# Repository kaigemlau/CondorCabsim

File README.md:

# Condor Cab Sim with Power Supply

Build with 15V symmetric power supply and active DI output (e.g. XLR)

Schematic and Layout created with KiCad 5

Original Design by Runoffgrove:
http://www.runoffgroove.com/condor.html

Works very well as an addon to the Anvil Preamp:
https://andyszeugs.wordpress.com/preamp-the-anvil/

## License: CC BY-NC-SA 3.0
Ref. original Condor Cab-Sim License:
https://creativecommons.org/licenses/by-nc-sa/3.0/

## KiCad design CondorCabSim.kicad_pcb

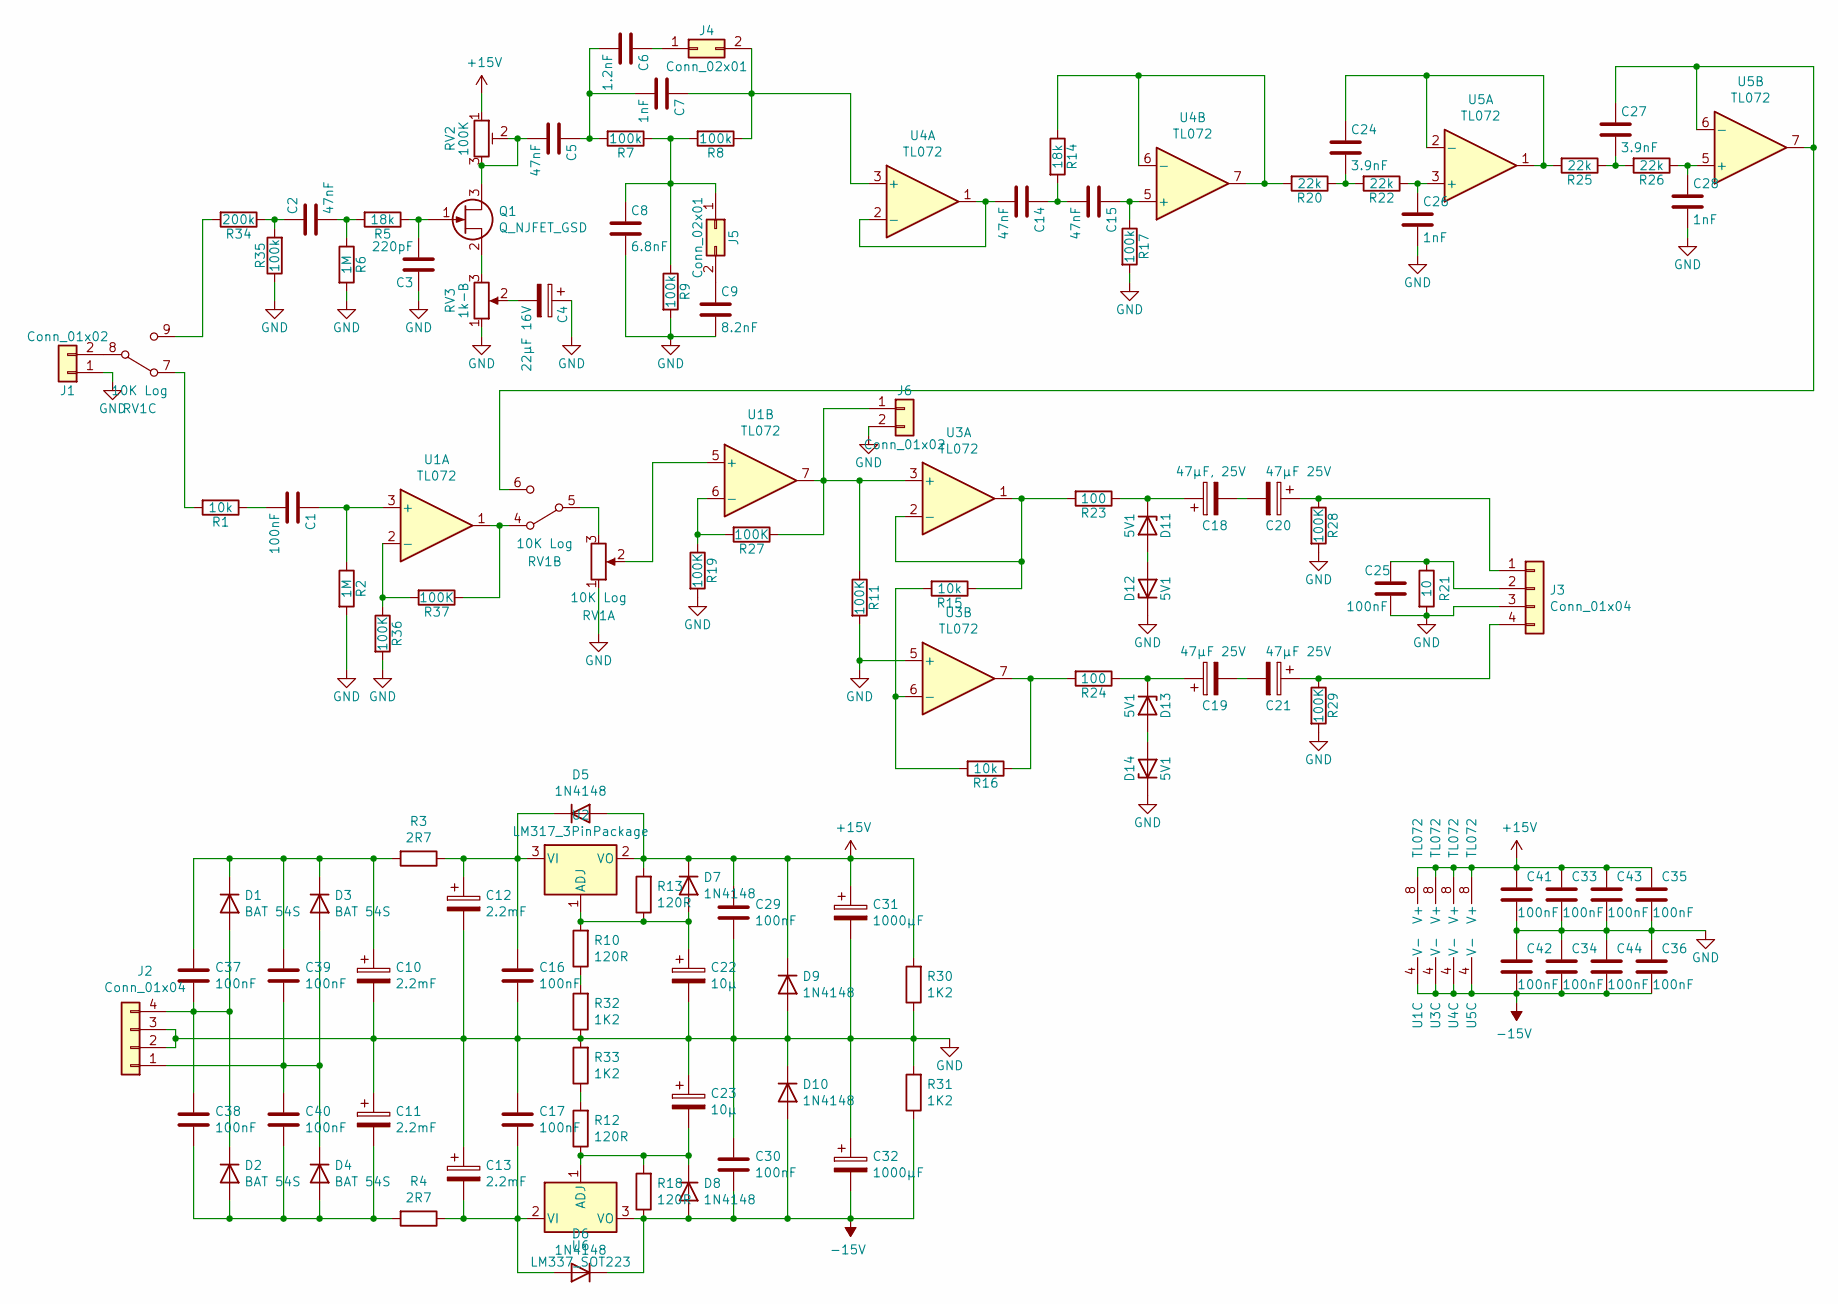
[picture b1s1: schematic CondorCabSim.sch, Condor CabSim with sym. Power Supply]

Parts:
C1: 100nF; C_Rect_L7.2mm_W2.5mm_P5.00mm_FKS2_FKP2_MKS2_MKP2
C2, C5, C14, C15: 47nF; C_Rect_L4.6mm_W3.0mm_P2.50mm_MKS02_FKP02
C3: 220pF; C_Rect_L4.6mm_W2.0mm_P2.50mm_MKS02_FKP02
C4: 22µF 16V; CP_Elec_4x5.8
C6: 1.2nF; C_Disc_D5.1mm_W3.2mm_P5.00mm
C7, C26, C28: 1nF; C_Rect_L4.6mm_W3.0mm_P2.50mm_MKS02_FKP02
C8: 6.8nF; C_Rect_L4.6mm_W3.0mm_P2.50mm_MKS02_FKP02
C9: 8.2nF; C_Disc_D5.1mm_W3.2mm_P5.00mm
C10, C11, C12, C13: 2.2mF; CP_Radial_D16.0mm_P7.50mm
C16, C17, C25, C29, C30, C33, C34, C35, C36, C37, C38, C39, C40, C41, C42, C43, C44: 100nF; C_0603_1608Metric
C18: 47µF, 25V; CP_Elec_6.3x5.8
C19, C20, C21: 47µF 25V; CP_Elec_6.3x5.8
C22, C23: 10µ; CP_Elec_5x5.9
C24, C27: 3.9nF; C_Disc_D5.1mm_W3.2mm_P5.00mm
C31, C32: 1000µF; CP_Radial_D10.0mm_P3.50mm
D1, D2, D3, D4: BAT 54S; D_DO-41_SOD81_P7.62mm_Horizontal
D5, D6, D7, D8, D9, D10: 1N4148; D_SOD-323F
D11, D12, D13, D14: 5V1; D_SOT-23_ANK
J1, J6: Conn_01x02; Molex_KK-254_AE-6410-02A_1x02_P2.54mm_Vertical
J2, J3: Conn_01x04; Molex_KK-254_AE-6410-04A_1x04_P2.54mm_Vertical
J4, J5: Conn_02x01; PinHeader_2x01_P2.54mm_Vertical
Q1: Q_NJFET_GSD; TO-92
R1, R15, R16: 10k; R_0603_1608Metric
R2, R6: 1M; R_0603_1608Metric
R3, R4: 2R7; R_1206_3216Metric
R5, R14: 18k; R_0603_1608Metric
R7, R8, R9, R17, R35: 100k; R_0603_1608Metric
R10, R12, R13, R18: 120R; R_0805_2012Metric
R11, R19, R27, R28, R29, R36, R37: 100K; R_0603_1608Metric
R20, R22, R25, R26: 22k; R_0603_1608Metric
R21: 10; R_0603_1608Metric
R23, R24: 100; R_0603_1608Metric
R30, R31: 1K2; R_1206_3216Metric
R32, R33: 1K2; R_0805_2012Metric
R34: 200k; R_0603_1608Metric
RV1: 10K Log; Potentiometer_Alpha_RV16BF-20_Single_Horizontal_DPDT
RV2: 100K; Potentiometer_Piher_PT-6-V_Vertical
RV3: 1k-B; Potentiometer_Alps_RK163_Single_Horizontal
U1, U3, U4, U5: TL072; SOIC-8_3.9x4.9mm_P1.27mm
U2: LM317_3PinPackage; SOT-223-3_TabPin2
U6: LM337_SOT223; SOT-223-3_TabPin2

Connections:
+15V: C29.1, C31.1, C33.1, C35.1, C41.1, C43.1, D5.2 (A), D7.1 (K), D9.1 (K), R13.2, R30.2, RV2.1, U1.8 (V+), U2.2 (VO), U3.8 (V+), U4.8 (V+), U5.8 (V+)
-15V: C30.2, C32.2, C34.2, C36.2, C42.2, C44.2, D6.1 (K), D8.2 (A), D10.2 (A), R18.1, R31.1, U1.4 (V-), U3.4 (V-), U4.4 (V-), U5.4 (V-), U6.3 (VO)
GND: C3.1, C4.1, C8.2, C9.2, C10.2, C11.1, C12.2, C13.1, C16.2, C17.1, C22.2, C23.1, C25.2, C26.2, C28.2, C29.2, C30.1, C31.2, C32.1, C33.2, C34.1, C35.2, C36.1, C41.2, C42.1, C43.2, C44.1, D9.2 (A), D10.1 (K), D12.1 (K), D14.1 (K), J1.1, J2.2, J2.3, J3.3, J6.2, R2.2, R6.2, R9.2, R11.2, R17.2, R19.2, R21.2, R28.2, R29.2, R30.1, R31.2, R32.1, R33.2, R35.1, R36.2, RV1.1, RV3.1, U3.5 (+)
unnamed: C1.1, R2.1, U1.3 (+)
unnamed: C1.2, R1.1
unnamed: C2.1, R34.1, R35.2
unnamed: C2.2, R5.2, R6.1
unnamed: C3.2, Q1.1 (G), R5.1
unnamed: C4.2, RV3.2
unnamed: C5.1, C6.2, C7.2, R7.2
unnamed: C5.2, Q1.3 (D), RV2.2, RV2.3
unnamed: C6.1, J4.1
unnamed: C7.1, J4.2, R8.1, U4.3 (+)
unnamed: C8.1, J5.1, R7.1, R8.2, R9.1
unnamed: C9.1, J5.2
unnamed: C10.1, C37.1, C39.1, D1.1 (K), D3.1 (K), R3.2
unnamed: C11.2, C38.2, C40.2, D2.2 (A), D4.2 (A), R4.2
unnamed: C12.1, C16.1, D5.1 (K), R3.1, U2.3 (VI)
unnamed: C13.2, C17.2, D6.2 (A), R4.1, U6.2 (VI)
unnamed: C14.1, C15.2, R14.2
unnamed: C14.2, U4.1, U4.2 (-)
unnamed: C15.1, R17.1, U4.5 (+)
unnamed: C18.1, D11.1 (K), R23.1
unnamed: C18.2, C20.2
unnamed: C19.1, D13.1 (K), R24.1
unnamed: C19.2, C21.2
unnamed: C20.1, J3.1, R28.1
unnamed: C21.1, J3.4, R29.1
unnamed: C22.1, D7.2 (A), R10.2, R13.1, U2.1 (ADJ)
unnamed: C23.2, D8.1 (K), R12.1, R18.2, U6.1 (ADJ)
unnamed: C24.1, R25.2, U5.1, U5.2 (-)
unnamed: C24.2, R20.1, R22.2
unnamed: C25.1, J3.2, R21.1
unnamed: C26.1, R22.1, U5.3 (+)
unnamed: C27.1, RV1.6, U5.6 (-), U5.7
unnamed: C27.2, R25.1, R26.2
unnamed: C28.1, R26.1, U5.5 (+)
unnamed: C37.2, C38.1, D1.2 (A), D2.1 (K), J2.4
unnamed: C39.2, C40.1, D3.2 (A), D4.1 (K), J2.1
unnamed: D11.2 (A), D12.2 (A)
unnamed: D13.2 (A), D14.2 (A)
unnamed: J1.2, RV1.8
unnamed: J6.1, R11.1, R27.1, U1.7, U3.3 (+)
unnamed: Q1.2 (S), RV3.3
unnamed: R1.2, RV1.7
unnamed: R10.1, R32.2
unnamed: R12.2, R33.1
unnamed: R14.1, R20.2, U4.6 (-), U4.7
unnamed: R15.1, R23.2, U3.1, U3.2 (-)
unnamed: R15.2, R16.2, U3.6 (-)
unnamed: R16.1, R24.2, U3.7
unnamed: R19.1, R27.2, U1.6 (-)
unnamed: R34.2, RV1.9
unnamed: R36.1, R37.2, U1.2 (-)
unnamed: R37.1, RV1.4, U1.1
unnamed: RV1.2, U1.5 (+)
unnamed: RV1.3, RV1.5

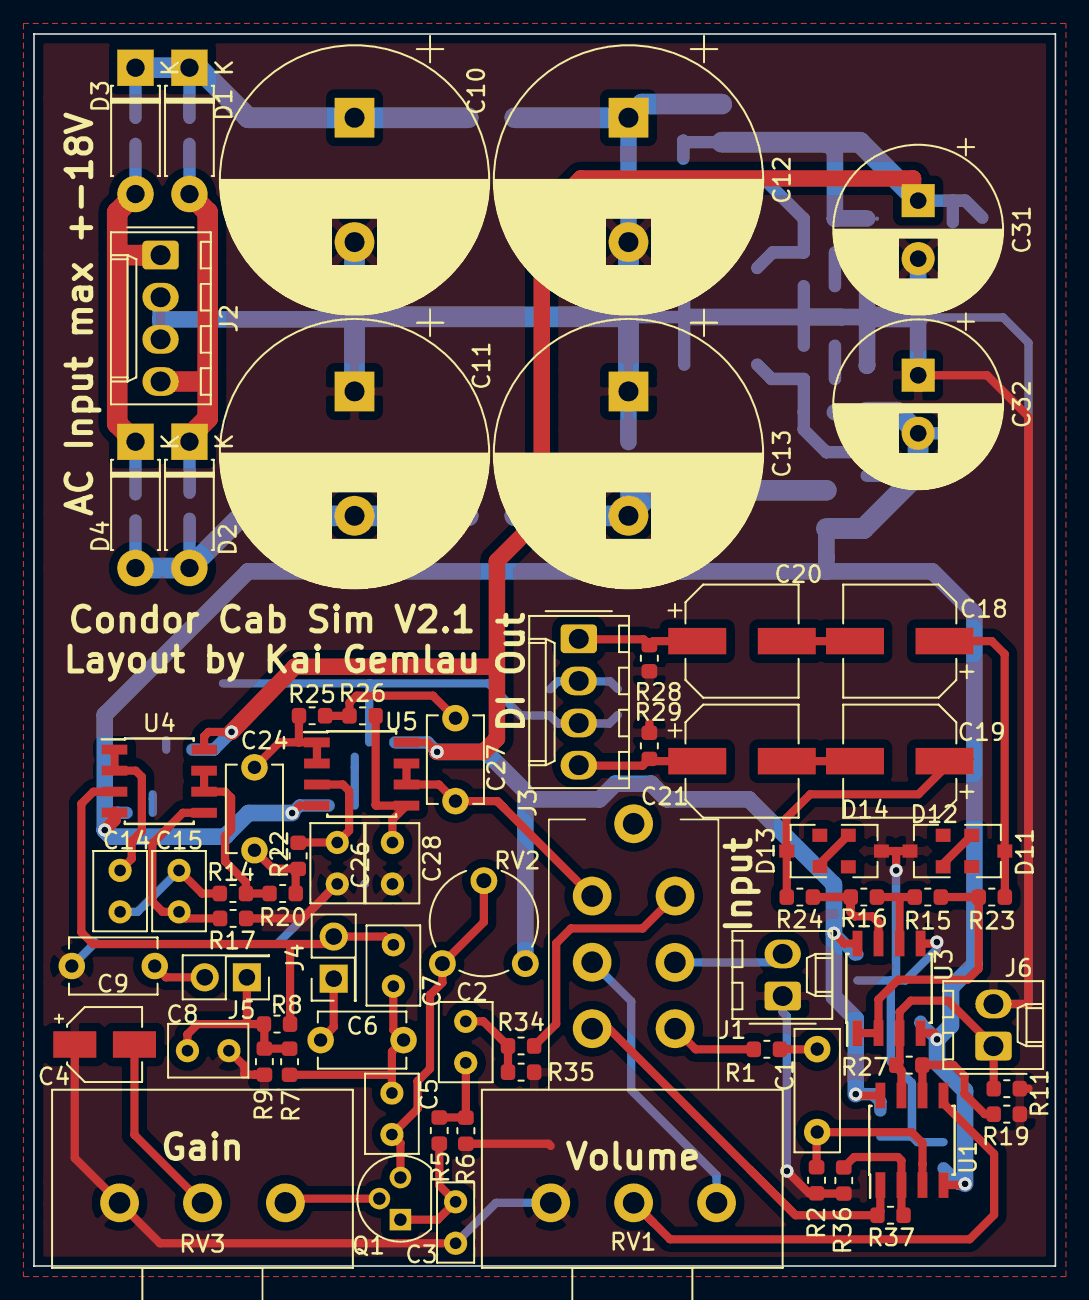
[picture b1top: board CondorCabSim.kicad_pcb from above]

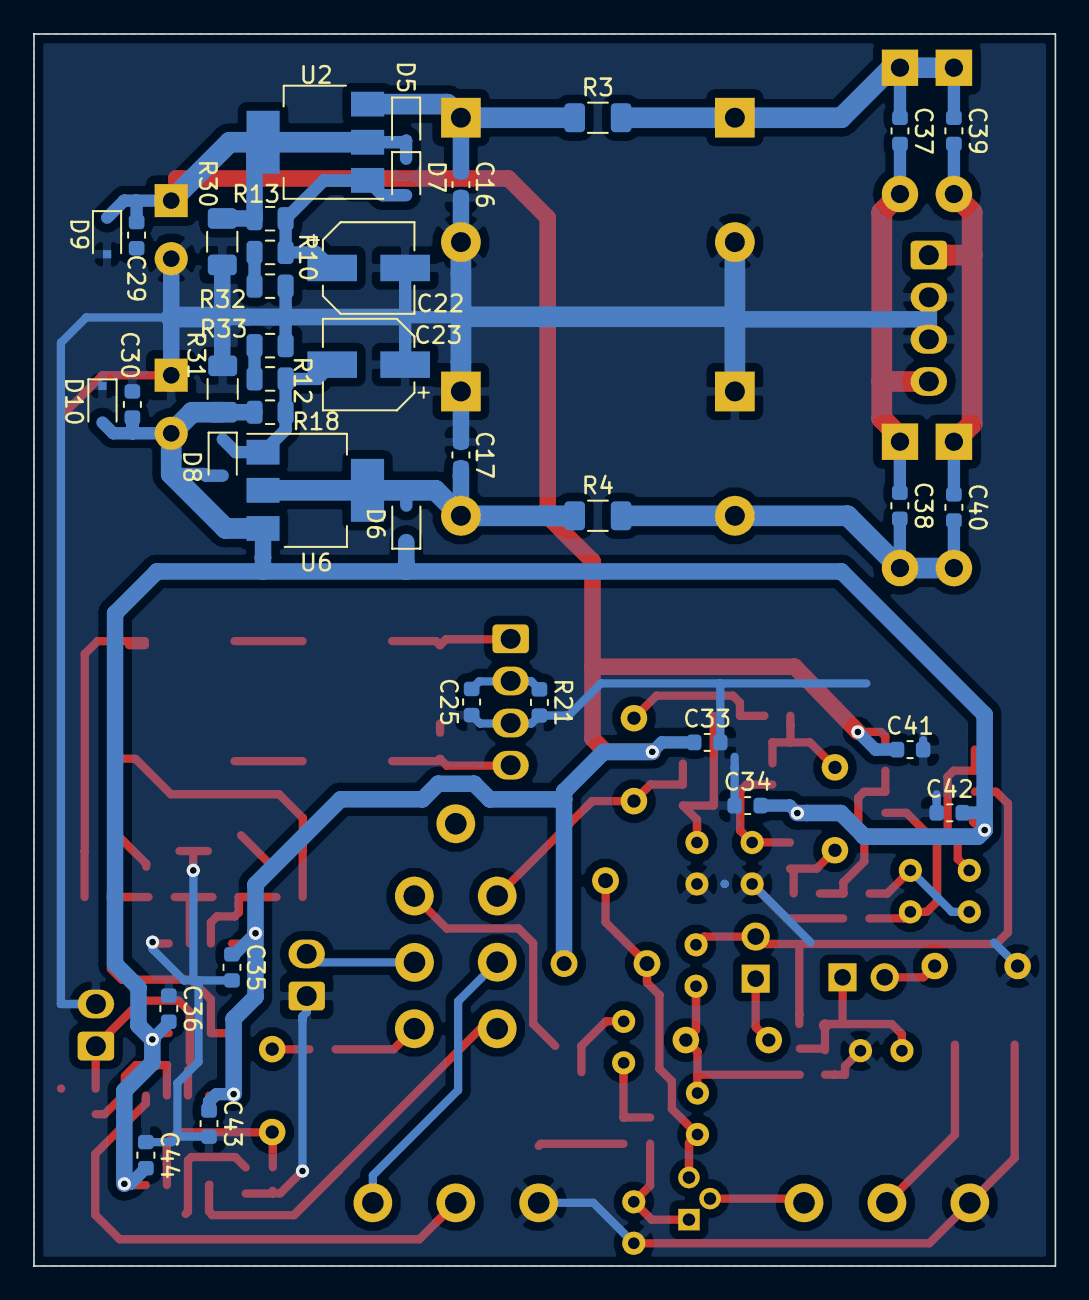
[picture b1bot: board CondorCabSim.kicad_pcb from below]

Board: 2 copper layers, 61.6 x 74.3 mm, 111 parts (38 on the bottom side), 57 nets.

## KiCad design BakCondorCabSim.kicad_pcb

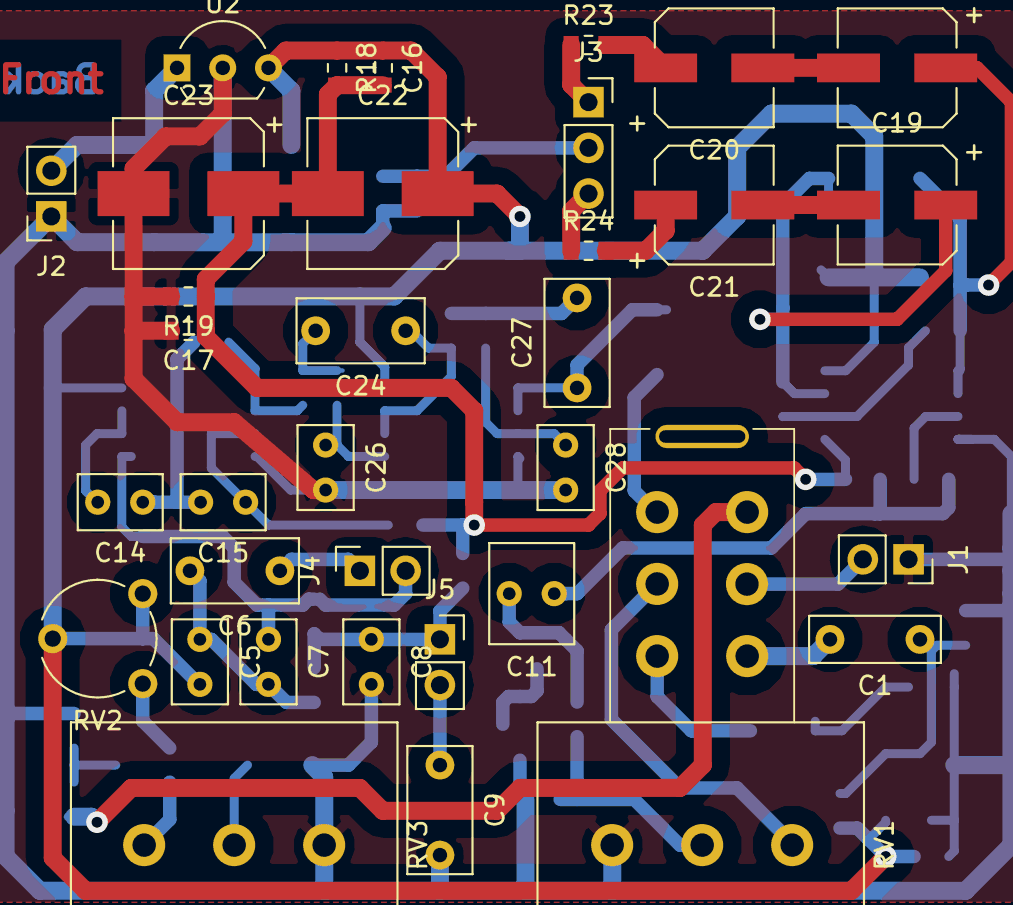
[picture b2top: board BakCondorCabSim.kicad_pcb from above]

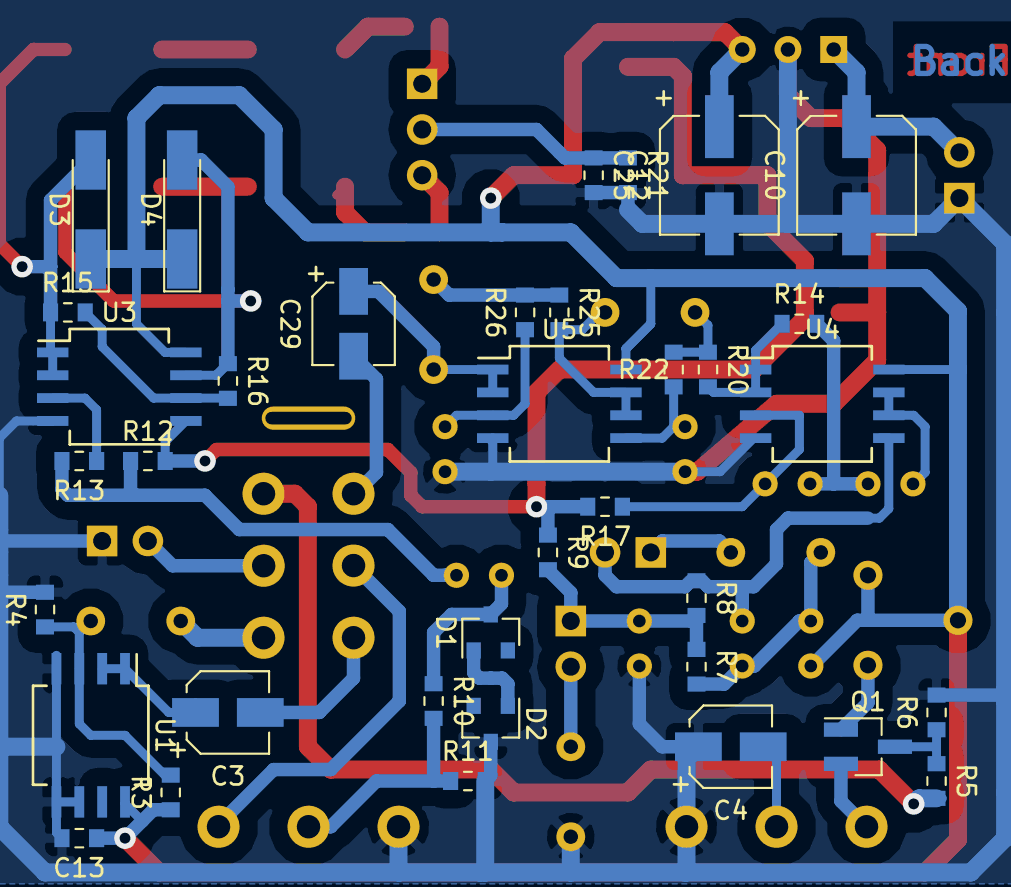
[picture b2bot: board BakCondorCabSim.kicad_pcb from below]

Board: 2 copper layers, 70 parts (36 on the bottom side), 46 nets.

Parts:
C1: 100nF; C_Rect_L7.2mm_W2.5mm_P5.00mm_FKS2_FKP2_MKS2_MKP2
C3, C4, C29: 22µF 16V; CP_Elec_4x5.8
C5, C14, C15: 47nF; C_Rect_L4.6mm_W3.0mm_P2.50mm_MKS02_FKP02
C6: 1.2nF; C_Rect_L7.0mm_W3.5mm_P5.00mm
C7, C26, C28: 1nF; C_Rect_L4.6mm_W3.0mm_P2.50mm_MKS02_FKP02
C8: 6.8nF; C_Rect_L4.6mm_W3.0mm_P2.50mm_MKS02_FKP02
C9: 8.2nF; C_Rect_L7.0mm_W3.5mm_P5.00mm
C10, C12: 100µF; CP_Elec_6.3x5.8
C11: 1µF; C_Rect_L4.6mm_W5.5mm_P2.50mm_MKS02_FKP02
C13, C16, C17, C25: 100nF; C_0603_1608Metric_Pad0.84x1.00mm_HandSolder
C18: 47µF, 25V; CP_Elec_6.3x5.8
C19, C20, C21: 47µF 25V; CP_Elec_6.3x5.8
C22, C23: 470µF 16V; CP_Elec_8x10.5
C24, C27: 3.9nF; C_Rect_L7.0mm_W3.5mm_P5.00mm
D1, D2: 5V1; D_SOT-23_ANK
D3, D4: 1N 4148; D_MiniMELF_Handsoldering
J1, J2: Conn_01x02; PinSocket_1x02_P2.54mm_Vertical
J3: Conn_01x03; PinSocket_1x03_P2.54mm_Vertical
J4, J5: Conn_02x01; PinSocket_1x02_P2.54mm_Vertical
Q1: MMBFJ201; SOT-23_Handsoldering
R3, R4, R6: 1M; R_0603_1608Metric_Pad0.84x1.00mm_HandSolder
R5, R14: 18k; R_0603_1608Metric_Pad0.84x1.00mm_HandSolder
R7, R8, R9, R17, R18, R19: 100k; R_0603_1608Metric_Pad0.84x1.00mm_HandSolder
R10: 2k2; R_0603_1608Metric_Pad0.84x1.00mm_HandSolder
R11, R12: 100K; R_0603_1608Metric_Pad0.84x1.00mm_HandSolder
R13: 1K; R_0603_1608Metric_Pad0.84x1.00mm_HandSolder
R15, R16: 10k; R_0603_1608Metric_Pad0.84x1.00mm_HandSolder
R20, R22, R25, R26: 22k; R_0603_1608Metric_Pad0.84x1.00mm_HandSolder
R21: 10; R_0603_1608Metric_Pad0.84x1.00mm_HandSolder
R23, R24: 100; R_0603_1608Metric_Pad0.84x1.00mm_HandSolder
RV1: 10K Log; Potentiometer_Alpha_RV16BF-20_Single_Horizontal_DPDT
RV2: 100K; Potentiometer_Piher_PT-6-V_Vertical
RV3: 1k-B; Potentiometer_Alps_RK163_Single_Horizontal
U1, U3, U4, U5: TL072; SO-8_5.3x6.2mm_P1.27mm
U2: 78L09; TO-92L_Inline_Wide

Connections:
+9V: C5.2, C12.1, C13.1, C16.1, C22.1, D3.1, D4.1, R3.1, R18.1, RV2.1, RV2.2, U1.8, U2.3, U3.8, U4.8, U5.8
GND: C4.1, C8.2, C9.2, C10.2, C12.2, C13.2, C17.2, C23.2, C25.2, C26.2, C28.2, D2.1, J1.1, J2.1, R4.2, R6.2, R11.2, R19.2, R21.2, RV1.1, RV3.3, U1.4, U1.5, U1.6, U2.2, U3.4, U4.4, U5.4
unnamed: C1.1, R3.2, R4.1, U1.3
unnamed: C1.2, RV1.7
unnamed: C3.1, U1.1, U1.2
unnamed: C3.2, RV1.4
unnamed: C4.2, RV3.2
unnamed: C5.1, C6.2, C7.2, R7.2
unnamed: C6.1, J4.1
unnamed: C7.1, J4.2, R8.1, U4.5
unnamed: C8.1, J5.1, R7.1, R8.2, R9.2
unnamed: C9.1, J5.2
unnamed: C10.1, J2.2, U2.1
unnamed: C11.1, R12.1, R13.2
unnamed: C11.2, D1.1, R10.1
unnamed: C14.1, C15.2, R14.2
unnamed: C14.2, U4.6, U4.7
unnamed: C15.1, R17.1, U4.3
unnamed: C18.1, D3.2, R15.1, U3.1, U3.2
unnamed: C18.2, C20.2
unnamed: C19.1, D4.2, R16.1, U3.7
unnamed: C19.2, C21.2
unnamed: C20.1, R23.2
unnamed: C21.1, R24.2
unnamed: C24.1, R25.2, U5.6, U5.7
unnamed: C24.2, R20.1, R22.2
unnamed: C25.1, J3.2, R21.1
unnamed: C26.1, R22.1, U5.5
unnamed: C27.1, C29.1, U5.1, U5.2
unnamed: C27.2, R25.1, R26.2
unnamed: C28.1, R26.1, U5.3
unnamed: C29.2, RV1.6
unnamed: D1.2, D2.2
unnamed: J1.2, RV1.8
unnamed: J3.1, R23.1
unnamed: J3.3, R24.1
unnamed: Q1.1, RV2.3
unnamed: Q1.2, RV3.1
unnamed: Q1.3, R5.1, R6.1
unnamed: R5.2, RV1.9
unnamed: R10.2, R11.1, RV1.2
unnamed: R13.1, U3.3
unnamed: R14.1, R20.2, U4.1, U4.2
unnamed: R15.2, R16.2, U3.6
unnamed: RV1.3, RV1.5
VAA: C16.2, C17.1, C22.2, C23.1, R9.1, R12.2, R17.2, R18.2, R19.1, U3.5

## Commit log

2020-09-26 Added files
